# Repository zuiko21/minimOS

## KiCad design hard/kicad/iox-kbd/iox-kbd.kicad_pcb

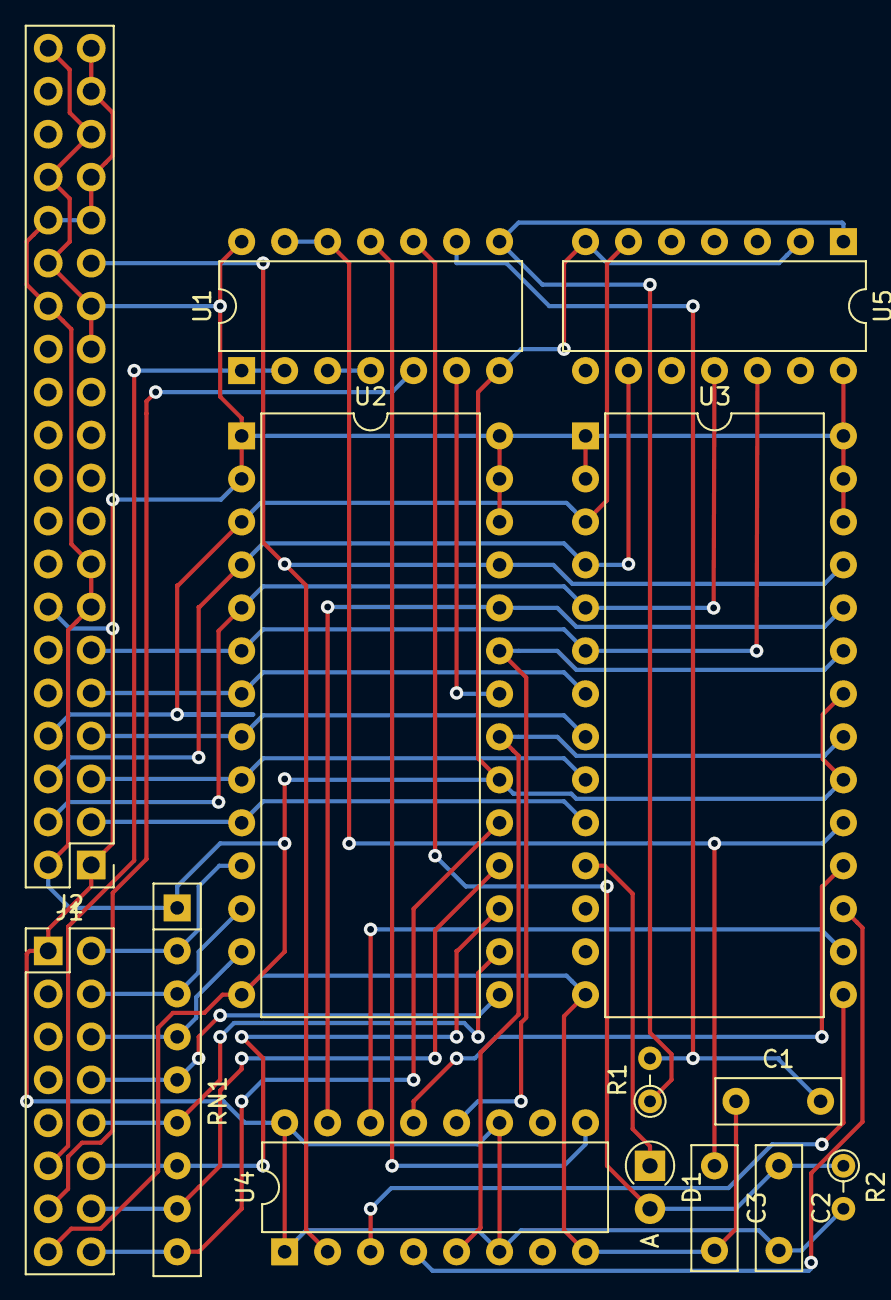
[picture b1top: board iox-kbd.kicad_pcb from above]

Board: 2 copper layers, 14 parts (0 on the bottom side), 36 nets.

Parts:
C1, C2, C3: C; C_Rect_L7.2mm_W2.5mm_P5.00mm_FKS2_FKP2_MKS2_MKP2
D1: 1N4148; D_A-405_P2.54mm_Vertical_AnodeUp
J1: IOX; PinHeader_2x08_P2.54mm_Vertical
J2: VIAport2; PinHeader_2x20_P2.54mm_Vertical
R1, R2: R; R_Axial_DIN0204_L3.6mm_D1.6mm_P2.54mm_Vertical
RN1: 220K; R_Array_SIP9
U1: 74HC132; DIP-14_W7.62mm
U2, U3: 27C512; DIP-28_W15.24mm
U4: 74HC174; DIP-16_W7.62mm
U5: 74HC4024; DIP-14_W7.62mm

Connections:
+5V: C2.2, J1.1, J2.1, J2.14, J2.25, J2.27, J2.30, J2.34, J2.35, J2.40, R2.2, U1.14, U2.1, U2.2, U2.26, U2.27, U2.28, U3.1, U3.2, U3.26, U3.27, U3.28, U4.1, U4.6, U4.11, U4.16, U5.14
/ALT: U3.18, U4.13
/CTL: U3.17, U4.4
/D0: J1.2, RN1.2, U2.11
/D1: J1.4, RN1.3, U2.12
/D2: J1.6, RN1.4, U2.13
/D3: J1.8, RN1.5, U2.15
/D4: J1.10, RN1.6, U2.16
/D5: J1.12, RN1.7, U2.17
/D6: J1.14, RN1.8, U2.18
/D7: J1.16, RN1.9, U2.19
/PA0: J2.3, U2.10, U3.10
/PA1: J2.5, U2.9, U3.9
/PA2: J2.7, U2.8, U3.8
/PA3: J2.9, U2.7, U3.7
/PA4: J2.11, U2.6, U3.6, U5.12
/PA5: J2.4, U2.5, U3.5, U5.11
/PA6: J2.6, U2.4, U3.4, U5.9
/PA7: J2.8, U2.3, U3.3, U5.6
/SHIFT: U3.16, U4.14
/~ACK: D1.1, U3.11
/~CAPS: U3.15, U4.3
/~CAPSLOCK: J2.29, U2.25, U3.25, U4.2
/~MOD: C3.1, U1.12, U1.13, U3.19
/~SEL: J1.11, U1.1, U1.2
/~WE: J1.13, U1.5
GND: C1.1, C3.2, J1.15, J2.2, J2.13, J2.15, J2.28, J2.31, J2.32, J2.33, J2.37, J2.39, RN1.1, U1.7, U2.14, U2.20, U3.14, U3.20, U3.22, U4.8, U5.2, U5.7
unnamed: C1.2, R1.2, U1.9
unnamed: C2.1, D1.2, R2.1, U1.10
unnamed: R1.1, U1.8, U5.1
unnamed: U1.3, U1.4
unnamed: U1.6, U2.22
unnamed: U1.11, U4.9
unnamed: U2.21, U3.21, U4.5
unnamed: U2.23, U3.23, U4.12
unnamed: U2.24, U3.24, U4.15

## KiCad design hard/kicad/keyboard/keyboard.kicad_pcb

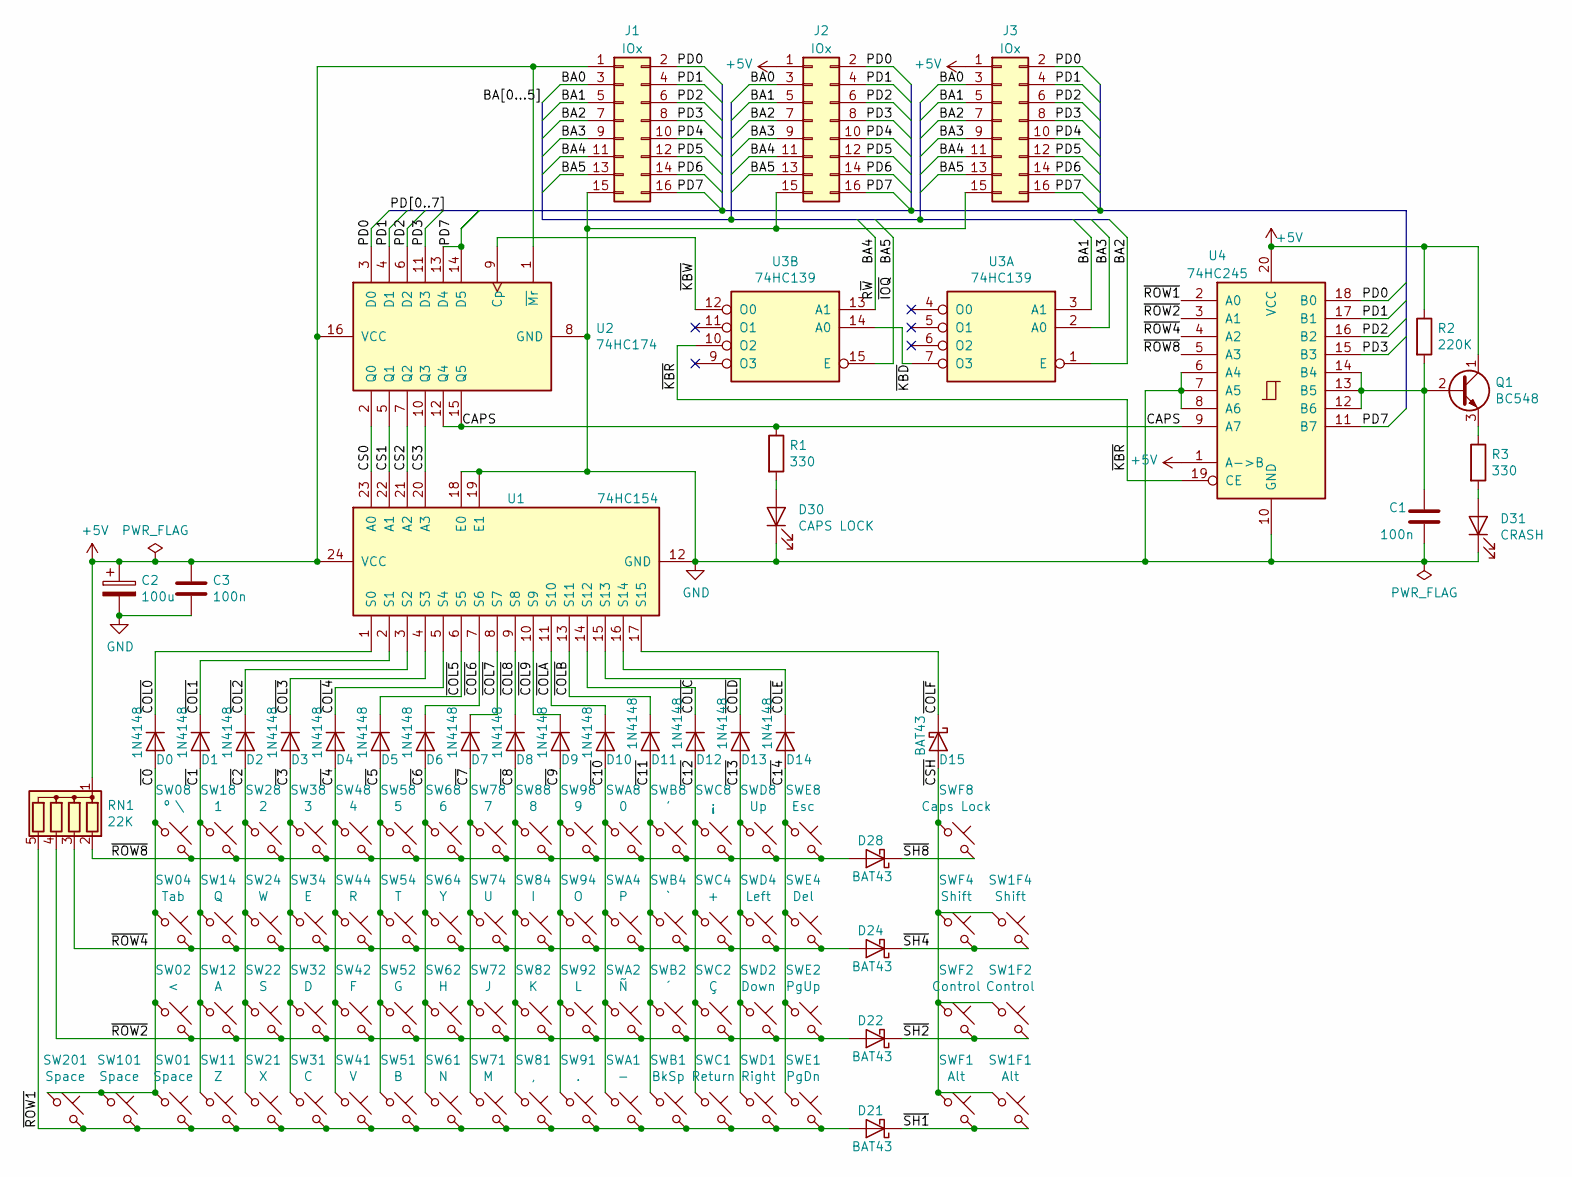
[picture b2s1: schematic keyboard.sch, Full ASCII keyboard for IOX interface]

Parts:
C1, C3: 100n; C_Rect_L7.2mm_W2.5mm_P5.00mm_FKS2_FKP2_MKS2_MKP2
C2: 100u; CP_Radial_D6.3mm_P2.50mm
D0, D1, D2, D3, D4, D5, D6, D7, D8, D9, D10, D11, D12, D13, D14: 1N4148; D_DO-35_SOD27_P7.62mm_Horizontal
D15, D21, D22, D24, D28: BAT43; D_DO-35_SOD27_P7.62mm_Horizontal
D30: CAPS LOCK; LED_D3.0mm
D31: CRASH; LED_D3.0mm
J1, J2, J3: IOx; IDC-Header_2x08_P2.54mm_Vertical
Q1: BC548; TO-92_Inline
R1, R3: 330; R_Axial_DIN0207_L6.3mm_D2.5mm_P10.16mm_Horizontal
R2: 220K; R_Axial_DIN0207_L6.3mm_D2.5mm_P10.16mm_Horizontal
RN1: 22K; R_Array_SIP5
SW01, SW101, SW201: Space; SW_PUSH-12mm
SW1F1: Alt; SW_PUSH-12mm
SW1F2: Control; SW_PUSH-12mm
SW1F4: Shift; SW_PUSH-12mm
SW02: <; SW_PUSH-12mm
SW04: Tab; SW_PUSH-12mm
SW08: º \\; SW_PUSH-12mm
SW11: Z; SW_PUSH-12mm
SW12: A; SW_PUSH-12mm
SW14: Q; SW_PUSH-12mm
SW18: 1; SW_PUSH-12mm
SW21: X; SW_PUSH-12mm
SW22: S; SW_PUSH-12mm
SW24: W; SW_PUSH-12mm
SW28: 2; SW_PUSH-12mm
SW31: C; SW_PUSH-12mm
SW32: D; SW_PUSH-12mm
SW34: E; SW_PUSH-12mm
SW38: 3; SW_PUSH-12mm
SW41: V; SW_PUSH-12mm
SW42: F; SW_PUSH-12mm
SW44: R; SW_PUSH-12mm
SW48: 4; SW_PUSH-12mm
SW51: B; SW_PUSH-12mm
SW52: G; SW_PUSH-12mm
SW54: T; SW_PUSH-12mm
SW58: 5; SW_PUSH-12mm
SW61: N; SW_PUSH-12mm
SW62: H; SW_PUSH-12mm
SW64: Y; SW_PUSH-12mm
SW68: 6; SW_PUSH-12mm
SW71: M; SW_PUSH-12mm
SW72: J; SW_PUSH-12mm
SW74: U; SW_PUSH-12mm
SW78: 7; SW_PUSH-12mm
SW81: ,; SW_PUSH-12mm
SW82: K; SW_PUSH-12mm
SW84: I; SW_PUSH-12mm
SW88: 8; SW_PUSH-12mm
SW91: .; SW_PUSH-12mm
SW92: L; SW_PUSH-12mm
SW94: O; SW_PUSH-12mm
SW98: 9; SW_PUSH-12mm
SWA1: -; SW_PUSH-12mm
SWA2: Ñ; SW_PUSH-12mm
SWA4: P; SW_PUSH-12mm
SWA8: 0; SW_PUSH-12mm
SWB1: BkSp; SW_PUSH-12mm
SWB2: ´; SW_PUSH-12mm
SWB4: `; SW_PUSH-12mm
SWB8: '; SW_PUSH-12mm
SWC1: Return; SW_PUSH-12mm
SWC2: Ç; SW_PUSH-12mm
SWC4: +; SW_PUSH-12mm
SWC8: ¡; SW_PUSH-12mm
SWD1: Right; SW_PUSH-12mm
SWD2: Down; SW_PUSH-12mm
SWD4: Left; SW_PUSH-12mm
SWD8: Up; SW_PUSH-12mm
SWE1: PgDn; SW_PUSH-12mm
SWE2: PgUp; SW_PUSH-12mm
SWE4: Del; SW_PUSH-12mm
SWE8: Esc; SW_PUSH-12mm
SWF1: Alt; SW_PUSH-12mm
SWF2: Control; SW_PUSH-12mm
SWF4: Shift; SW_PUSH-12mm
SWF8: Caps Lock; SW_PUSH-12mm
U1: 74HC154; DIP-24_W7.62mm_Socket
U2: 74HC174; DIP-16_W7.62mm_Socket
U3: 74HC139; DIP-16_W7.62mm_Socket
U4: 74HC245; DIP-20_W7.62mm

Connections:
+5V: C2.1, C3.1, J1.1, J2.1, J3.1, Q1.1 (C), R2.1, RN1.1 (common), U1.24 (VCC), U2.1 (~Mr), U2.16 (VCC), U4.1 (A->B), U4.20 (VCC)
/BA0: J1.3, J2.3, J3.3
/BA1: J1.5, J2.5, J3.5, U3.3 (A1)
/BA2: J1.7, J2.7, J3.7, U3.1 (E)
/BA3: J1.9, J2.9, J3.9, U3.2 (A0)
/BA4: J1.11, J2.11, J3.11, U3.13 (A1)
/BA5: J1.13, J2.13, J3.13, U3.15 (E)
/CAPS: R1.1, U2.12 (Q4), U2.15 (Q5), U4.9 (A7)
/CS0: U1.23 (A0), U2.2 (Q0)
/CS1: U1.22 (A1), U2.5 (Q1)
/CS2: U1.21 (A2), U2.7 (Q2)
/CS3: U1.20 (A3), U2.10 (Q3)
/PD0: J1.2, J2.2, J3.2, U2.3 (D0), U4.18 (B0)
/PD1: J1.4, J2.4, J3.4, U2.4 (D1), U4.17 (B1)
/PD2: J1.6, J2.6, J3.6, U2.6 (D2), U4.16 (B2)
/PD3: J1.8, J2.8, J3.8, U2.11 (D3), U4.15 (B3)
/PD4: J1.10, J2.10, J3.10
/PD5: J1.12, J2.12, J3.12
/PD6: J1.14, J2.14, J3.14
/PD7: J1.16, J2.16, J3.16, U2.13 (D4), U2.14 (D5), U4.11 (B7)
/~C0: D0.2 (A), SW01.1, SW02.1, SW04.1, SW08.1, SW101.1, SW201.1
/~C1: D1.2 (A), SW11.1, SW12.1, SW14.1, SW18.1
/~C2: D2.2 (A), SW21.1, SW22.1, SW24.1, SW28.1
/~C3: D3.2 (A), SW31.1, SW32.1, SW34.1, SW38.1
/~C4: D4.2 (A), SW41.1, SW42.1, SW44.1, SW48.1
/~C5: D5.2 (A), SW51.1, SW52.1, SW54.1, SW58.1
/~C6: D6.2 (A), SW61.1, SW62.1, SW64.1, SW68.1
/~C7: D7.2 (A), SW71.1, SW72.1, SW74.1, SW78.1
/~C8: D8.2 (A), SW81.1, SW82.1, SW84.1, SW88.1
/~C9: D9.2 (A), SW91.1, SW92.1, SW94.1, SW98.1
/~C10: D10.2 (A), SWA1.1, SWA2.1, SWA4.1, SWA8.1
/~C11: D11.2 (A), SWB1.1, SWB2.1, SWB4.1, SWB8.1
/~C12: D12.2 (A), SWC1.1, SWC2.1, SWC4.1, SWC8.1
/~C13: D13.2 (A), SWD1.1, SWD2.1, SWD4.1, SWD8.1
/~C14: D14.2 (A), SWE1.1, SWE2.1, SWE4.1, SWE8.1
/~COL0: D0.1 (K), U1.1 (S0)
/~COL1: D1.1 (K), U1.2 (S1)
/~COL2: D2.1 (K), U1.3 (S2)
/~COL3: D3.1 (K), U1.4 (S3)
/~COL4: D4.1 (K), U1.5 (S4)
/~COL5: D5.1 (K), U1.6 (S5)
/~COL6: D6.1 (K), U1.7 (S6)
/~COL7: D7.1 (K), U1.8 (S7)
/~COL8: D8.1 (K), U1.9 (S8)
/~COL9: D9.1 (K), U1.10 (S9)
/~COLA: D10.1 (K), U1.11 (S10)
/~COLB: D11.1 (K), U1.13 (S11)
/~COLC: D12.1 (K), U1.14 (S12)
/~COLD: D13.1 (K), U1.15 (S13)
/~COLE: D14.1 (K), U1.16 (S14)
/~COLF: D15.1 (K), U1.17 (S15)
/~CSH: D15.2 (A), SW1F1.1, SW1F2.1, SW1F4.1, SWF1.1, SWF2.1, SWF4.1, SWF8.1
/~KBD: U3.7 (O3), U3.14 (A0)
/~KBR: U3.10 (O2), U4.19 (CE)
/~KBW: U2.9 (Cp), U3.12 (O0)
/~ROW1: D21.2 (A), RN1.5 (R4), SW01.2, SW11.2, SW21.2, SW31.2, SW41.2, SW51.2, SW61.2, SW71.2, SW81.2, SW91.2, SW101.2, SW201.2, SWA1.2, SWB1.2, SWC1.2, SWD1.2, SWE1.2, U4.2 (A0)
/~ROW2: D22.2 (A), RN1.4 (R3), SW02.2, SW12.2, SW22.2, SW32.2, SW42.2, SW52.2, SW62.2, SW72.2, SW82.2, SW92.2, SWA2.2, SWB2.2, SWC2.2, SWD2.2, SWE2.2, U4.3 (A1)
/~ROW4: D24.2 (A), RN1.3 (R2), SW04.2, SW14.2, SW24.2, SW34.2, SW44.2, SW54.2, SW64.2, SW74.2, SW84.2, SW94.2, SWA4.2, SWB4.2, SWC4.2, SWD4.2, SWE4.2, U4.4 (A2)
/~ROW8: D28.2 (A), RN1.2 (R1), SW08.2, SW18.2, SW28.2, SW38.2, SW48.2, SW58.2, SW68.2, SW78.2, SW88.2, SW98.2, SWA8.2, SWB8.2, SWC8.2, SWD8.2, SWE8.2, U4.5 (A3)
/~SH1: D21.1 (K), SW1F1.2, SWF1.2
/~SH2: D22.1 (K), SW1F2.2, SWF2.2
/~SH4: D24.1 (K), SW1F4.2, SWF4.2
/~SH8: D28.1 (K), SWF8.2
GND: C1.2, C2.2, C3.2, D30.1 (K), D31.1 (K), J1.15, J2.15, J3.15, U1.12 (GND), U1.18 (E0), U1.19 (E1), U2.8 (GND), U4.6 (A4), U4.7 (A5), U4.8 (A6), U4.10 (GND)
unnamed: C1.1, Q1.2 (B), R2.2, U4.12 (B6), U4.13 (B5), U4.14 (B4)
unnamed: D30.2 (A), R1.2
unnamed: D31.2 (A), R3.2
unnamed: Q1.3 (E), R3.1

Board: 2 copper layers, 106 parts (0 on the bottom side), 68 nets, no tracks yet.

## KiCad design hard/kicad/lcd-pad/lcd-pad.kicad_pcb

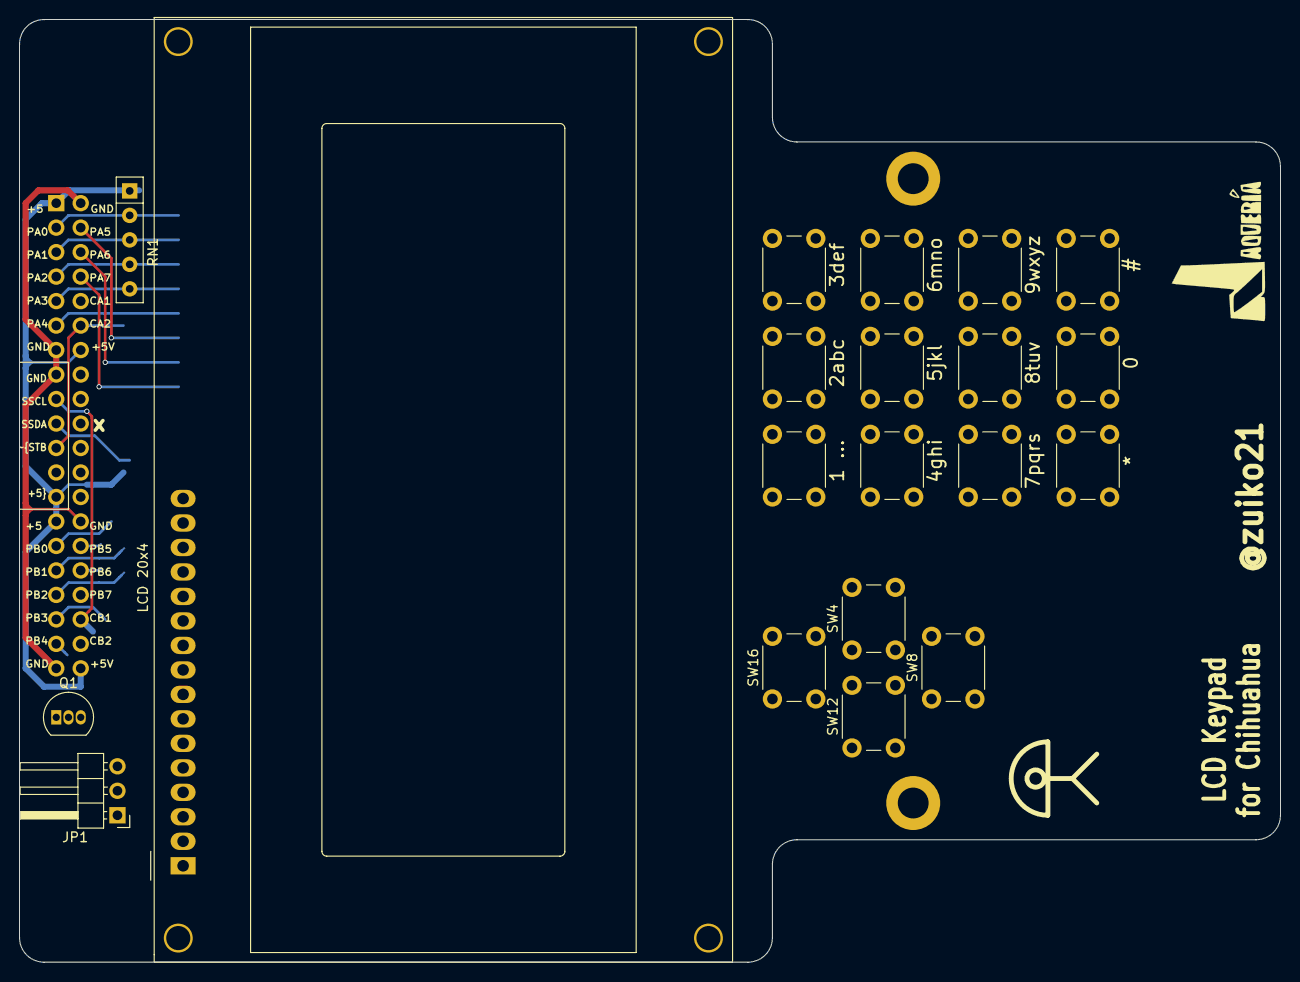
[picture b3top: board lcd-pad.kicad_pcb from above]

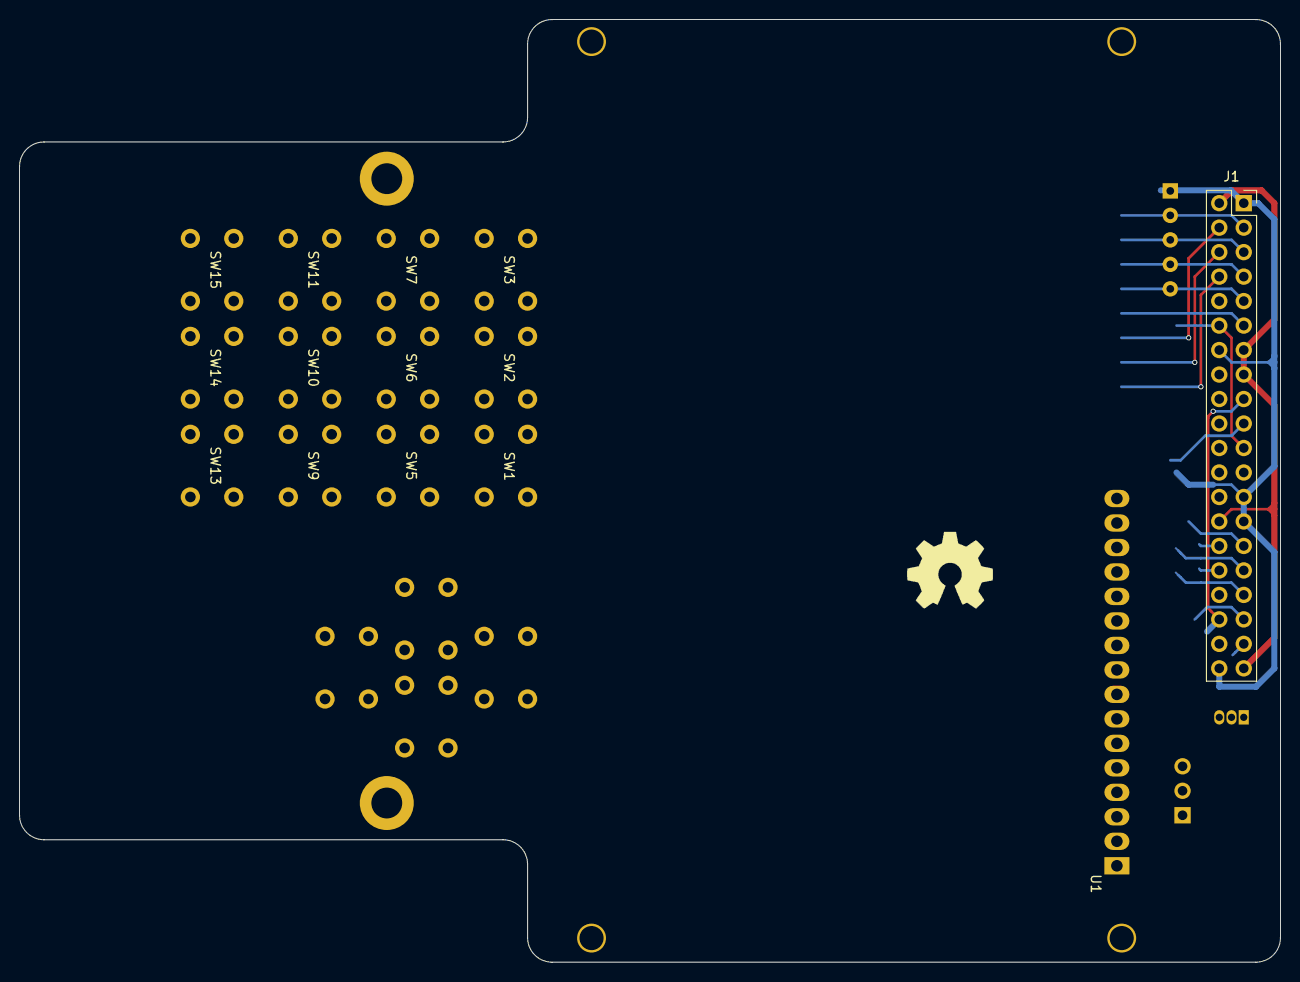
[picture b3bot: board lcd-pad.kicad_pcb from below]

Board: 2 copper layers, 130.8 x 97.8 mm, 25 parts (2 on the bottom side), 22 nets.

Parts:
H1, H2: MountingHole_Pad; MountingHole_3.2mm_M3_DIN965_Pad
J1: VIAport; PinSocket_2x20_P2.54mm_Vertical
JP1: AUTO/ON; PinHeader_1x03_P2.54mm_Horizontal
LOGO1: Logo_Open_Hardware_Large; OSHW-Symbol_8.9x8mm_SilkScreen
LOGO2: Logo_Open_Hardware_Small; jaqueria
Q1: BC558; TO-92_Inline
RN1: 4K7; R_Array_SIP5
SW1: 1 …; SW_PUSH_6mm
SW2: 2abc; SW_PUSH_6mm
SW3: 3def; SW_PUSH_6mm
SW4: Right; SW_PUSH_6mm
SW5: 4ghi; SW_PUSH_6mm
SW6: 5jkl; SW_PUSH_6mm
SW7: 6mno; SW_PUSH_6mm
SW8: Down; SW_PUSH_6mm
SW9: 7pqrs; SW_PUSH_6mm
SW10: 8tuv; SW_PUSH_6mm
SW11: 9wxyz; SW_PUSH_6mm
SW12: Left; SW_PUSH_6mm
SW13: *; SW_PUSH_6mm
SW14: 0; SW_PUSH_6mm
SW15: #; SW_PUSH_6mm
SW16: Up; SW_PUSH_6mm
U1: LCD 20x4; JHD204AO_LCD20x4

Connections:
+5V: J1.1, J1.14, J1.25, J1.27, J1.40, RN1.1, U1.2, U1.15
/BUF_LED: JP1.1, Q1.3
/CA2: J1.12, J1.21
/CB1: J1.17, J1.36
/CB2: J1.19, J1.38, Q1.2
/LED_K: JP1.2, U1.16
GND: H1.1, H2.1, J1.2, J1.13, J1.15, J1.28, J1.39, JP1.3, Q1.1, U1.1
PA0: J1.3, RN1.2, SW1.2, SW2.2, SW3.2, SW4.2
PA1: J1.5, RN1.3, SW5.2, SW6.2, SW7.2, SW8.2
PA2: J1.7, RN1.4, SW9.2, SW10.2, SW11.2, SW12.2
PA3: J1.9, RN1.5, SW13.2, SW14.2, SW15.2, SW16.2
PA4: J1.11, SW1.1, SW5.1, SW9.1, SW13.1
PA5: J1.4, SW2.1, SW6.1, SW10.1, SW14.1
PA6: J1.6, SW3.1, SW7.1, SW11.1, SW15.1
PA7: J1.8, SW4.1, SW8.1, SW12.1, SW16.1
PB0: J1.29, U1.6
PB1: J1.31, U1.4
PB2: J1.33, U1.5
PB4: J1.37, U1.11
PB5: J1.30, U1.12
PB6: J1.32, U1.13
PB7: J1.34, U1.14

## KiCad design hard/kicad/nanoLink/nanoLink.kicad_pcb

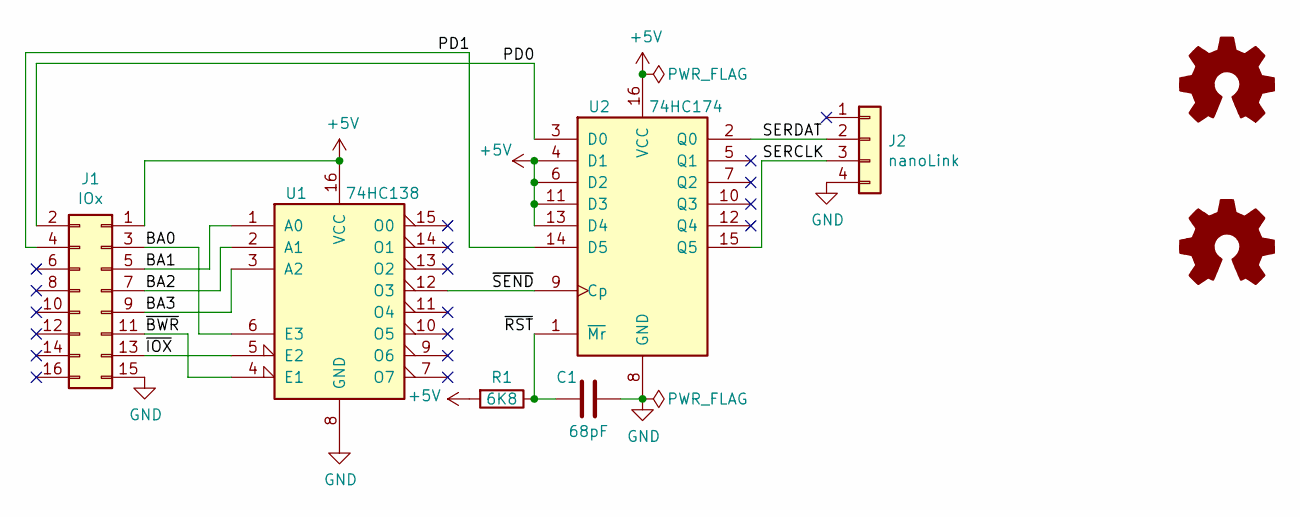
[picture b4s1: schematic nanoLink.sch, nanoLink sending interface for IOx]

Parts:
C1: 68pF; C_Disc_D3.8mm_W2.6mm_P2.50mm
J1: IOx; PinSocket_2x08_P2.54mm_Horizontal
J2: nanoLink; PinHeader_1x04_P2.54mm_Horizontal
LOGO1: Logo_Open_Hardware_Small; OSHW-Logo2_7.3x6mm_SilkScreen
LOGO2: Logo_Open_Hardware_Small; j300
R1: 6K8; R_Axial_DIN0207_L6.3mm_D2.5mm_P2.54mm_Vertical
U1: 74HC138; DIP-16_W7.62mm_Socket
U2: 74HC174; DIP-16_W7.62mm_Socket

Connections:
+5V: J1.1, R1.2, U1.16 (VCC), U2.4 (D1), U2.6 (D2), U2.11 (D3), U2.13 (D4), U2.16 (VCC)
/BA0: J1.3, U1.6 (E3)
/BA1: J1.5, U1.1 (A0)
/BA2: J1.7, U1.2 (A1)
/BA3: J1.9, U1.3 (A2)
/PD0: J1.2, U2.3 (D0)
/PD1: J1.4, U2.14 (D5)
/SERCLK: J2.3, U2.15 (Q5)
/SERDAT: J2.2, U2.2 (Q0)
/~BWR: J1.11, U1.4 (E1)
/~IOX: J1.13, U1.5 (E2)
/~RST: C1.2, R1.1, U2.1 (~Mr)
/~SEND: U1.12 (O3), U2.9 (Cp)
GND: C1.1, J1.15, J2.4, U1.8 (GND), U2.8 (GND)

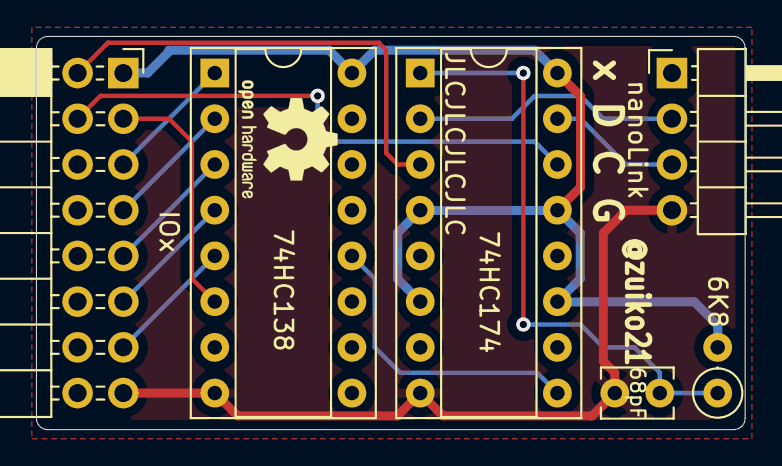
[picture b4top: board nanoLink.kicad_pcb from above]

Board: 2 copper layers, 39.4 x 21.8 mm, 8 parts (1 on the bottom side), 14 nets.

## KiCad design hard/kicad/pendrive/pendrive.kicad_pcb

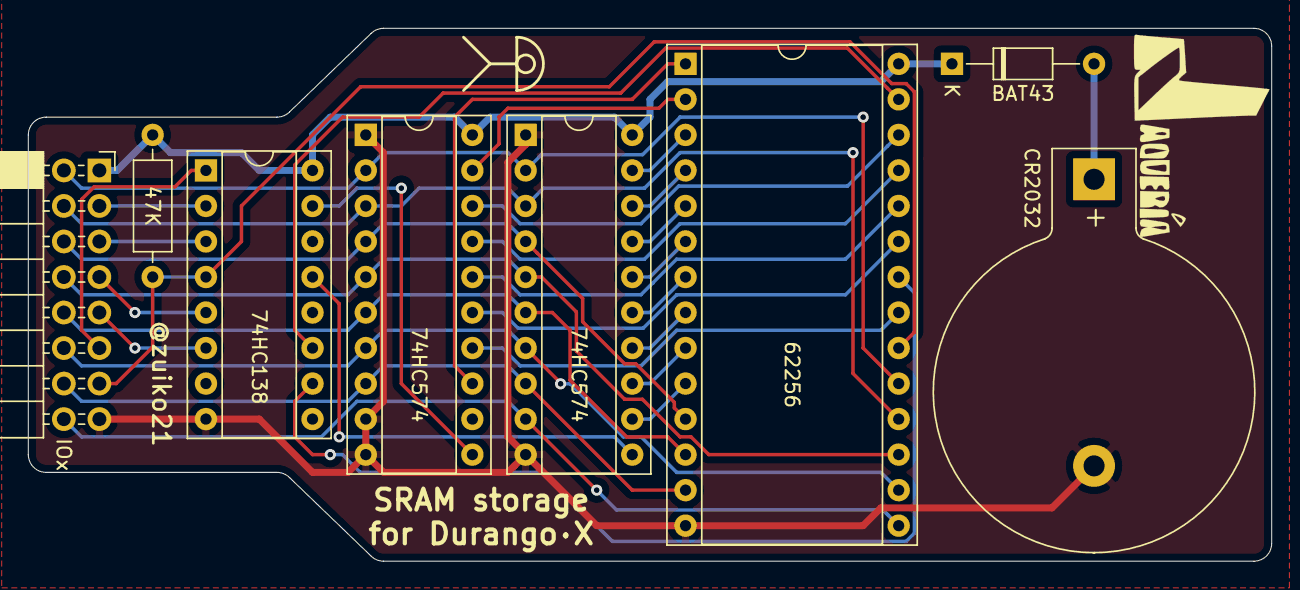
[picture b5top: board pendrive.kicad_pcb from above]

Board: 2 copper layers, 88.9 x 38.1 mm, 10 parts (1 on the bottom side), 36 nets.

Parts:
BT1: CR2032; BatteryHolder_Keystone_103_1x20mm
D1: BAT43; D_DO-35_SOD27_P10.16mm_Horizontal
J1: IOx; PinSocket_2x08_P2.54mm_Horizontal
LOGO1: Logo_Open_Hardware_Small; jaqueria
LOGO2: Logo_Open_Hardware_Large; OSHW-Logo_19x20mm_SilkScreen
R1: 47K; R_Axial_DIN0207_L6.3mm_D2.5mm_P10.16mm_Horizontal
U1: 62256; DIP-28_W15.24mm_Socket
U2: 74HC138; DIP-16_W7.62mm_Socket
U3, U4: 74HC574; DIP-20_W7.62mm_Socket

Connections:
+5V: D1.1, J1.1, R1.2, U1.28, U2.16, U3.20, U4.20
/A0: U1.3, U3.19
/A1: U1.4, U3.18
/A2: U1.5, U3.17
/A3: U1.6, U3.16
/A4: U1.7, U3.15
/A5: U1.8, U3.14
/A6: U1.9, U3.13
/A7: U1.10, U3.12
/A8: U1.2, U4.19
/A9: U1.26, U4.18
/A10: U1.25, U4.17
/A11: U1.24, U4.16
/A12: U1.23, U4.15
/A13: U1.21, U4.14
/A14: U1.1, U4.13
/BA0: J1.3, U2.2
/BA1: J1.5, U2.3
/BA2: J1.7, U2.5
/BA3: J1.9, U2.6
/PD0: J1.2, U1.19, U3.2, U4.2
/PD1: J1.4, U1.18, U3.3, U4.3
/PD2: J1.6, U1.11, U3.4, U4.4
/PD3: J1.8, U1.17, U3.5, U4.5
/PD4: J1.10, U1.12, U3.6, U4.6
/PD5: J1.12, U1.16, U3.7, U4.7
/PD6: J1.14, U1.13, U3.8, U4.8
/PD7: J1.16, U1.15, U3.9
/~BRW: J1.11, U2.1
/~IOX: J1.13, R1.1, U1.20, U2.4
/~LH: U2.15, U4.11
/~LL: U2.13, U3.11
/~OE: U1.22, U2.10
/~WE: U1.27, U2.11
GND: BT1.2, J1.15, U1.14, U2.8, U3.1, U3.10, U4.1, U4.9, U4.10
unnamed: BT1.1, D1.2

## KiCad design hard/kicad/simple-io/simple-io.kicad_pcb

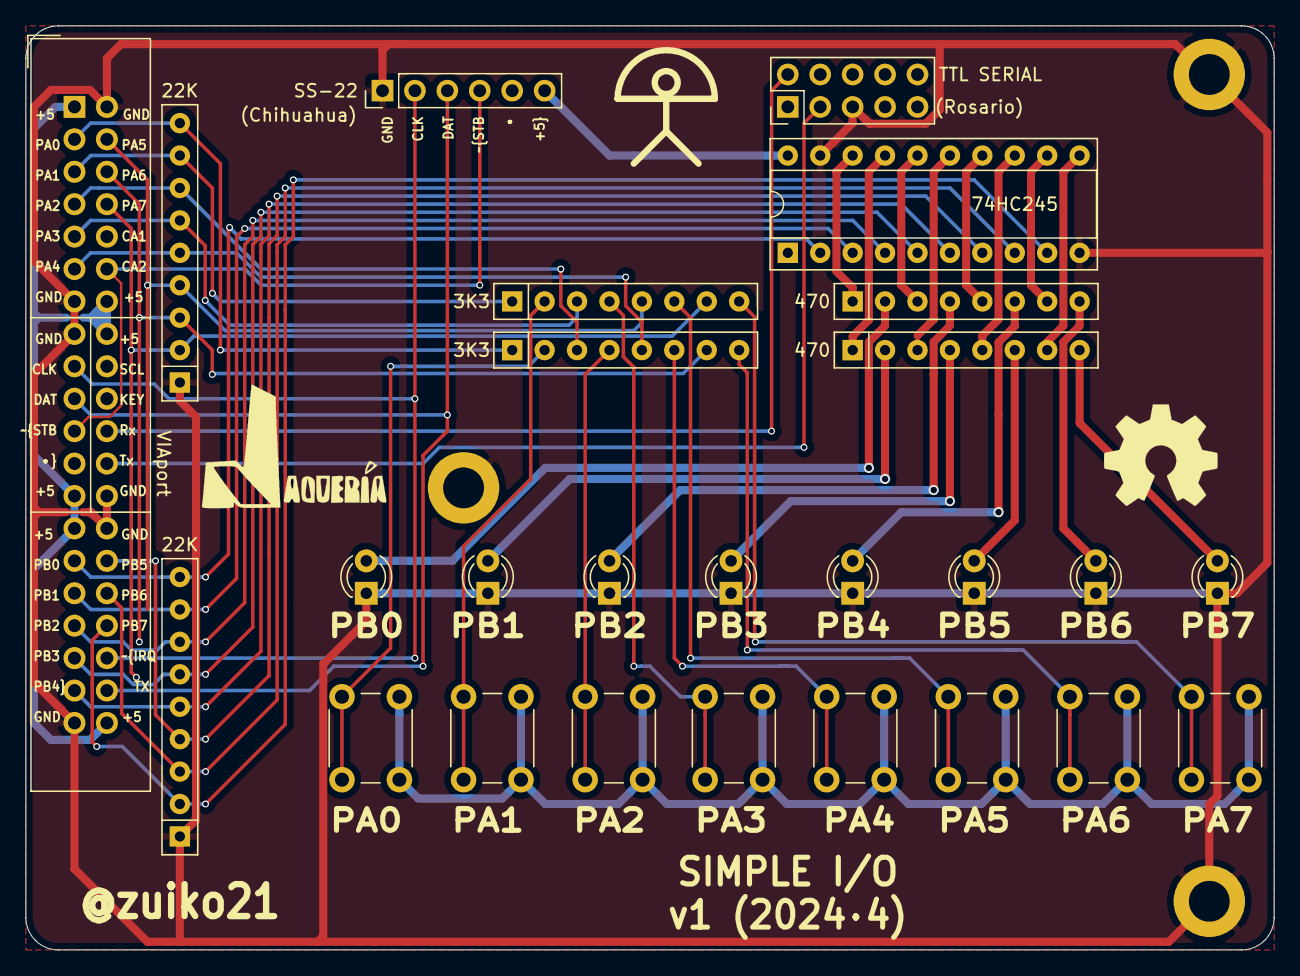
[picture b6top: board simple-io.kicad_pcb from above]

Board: 2 copper layers, 97.8 x 72.4 mm, 31 parts (0 on the bottom side), 47 nets.

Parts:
D1: PB0; LED_D3.0mm
D2: PB1; LED_D3.0mm
D3: PB2; LED_D3.0mm
D4: PB3; LED_D3.0mm
D5: PB4; LED_D3.0mm
D6: PB5; LED_D3.0mm
D7: PB6; LED_D3.0mm
D8: PB7; LED_D3.0mm
H1, H2, H3: MountingHole_Pad; MountingHole_3.2mm_M3_DIN965_Pad
J1: SS-22; PinHeader_1x06_P2.54mm_Vertical
J2: VIAport; IDC-Header_2x20_P2.54mm_Vertical
J3: TTL SERIAL; PinHeader_2x05_P2.54mm_Vertical
LOGO1: Logo_Open_Hardware_Large; OSHW-Symbol_8.9x8mm_SilkScreen
LOGO2: Logo_Open_Hardware_Small; jaqueria
RN1, RN6: 22K; R_Array_SIP9
RN2, RN3: 3K3; R_Array_SIP8
RN4, RN5: 470; R_Array_SIP8
SW1: PA0; SW_PUSH_6mm_H5mm
SW2: PA1; SW_PUSH_6mm_H5mm
SW3: PA2; SW_PUSH_6mm_H5mm
SW4: PA3; SW_PUSH_6mm_H5mm
SW5: PA4; SW_PUSH_6mm_H5mm
SW6: PA5; SW_PUSH_6mm_H5mm
SW7: PA6; SW_PUSH_6mm_H5mm
SW8: PA7; SW_PUSH_6mm_H5mm
U1: 74HC245; DIP-20_W7.62mm_Socket

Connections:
+5V: J1.6, J2.1, J2.14, J2.16, J2.25, J2.27, J2.40, SW1.2, SW2.2, SW3.2, SW4.2, SW5.2, SW6.2, SW7.2, SW8.2, U1.1, U1.20
/BB0: RN4.1, U1.18
/BB1: RN5.1, U1.17
/BB2: RN4.3, U1.16
/BB3: RN5.3, U1.15
/BB4: RN4.5, U1.14
/BB5: RN5.5, U1.13
/BB6: RN4.7, U1.12
/BB7: RN5.7, U1.11
/CA2: J1.4, J2.12, J2.21
/CB1: J1.2, J2.17, J2.36
/CB2: J1.3, J2.19, J2.38
/RA0: RN3.2, SW1.1
/RA1: RN2.2, SW2.1
/RA2: RN3.4, SW3.1
/RA3: RN2.4, SW4.1
/RA4: RN3.6, SW5.1
/RA5: RN2.6, SW6.1
/RA6: RN3.8, SW7.1
/RA7: RN2.8, SW8.1
/RB0: D1.2, RN4.2
/RB1: D2.2, RN5.2
/RB2: D3.2, RN4.4
/RB3: D4.2, RN5.4
/RB4: D5.2, RN4.6
/RB5: D6.2, RN5.6
/RB6: D7.2, RN4.8
/RB7: D8.2, RN5.8
/SC_RX: J2.22, J3.2
/SC_TX: J2.24, J3.3
GND: D1.1, D2.1, D3.1, D4.1, D5.1, D6.1, D7.1, D8.1, H1.1, H2.1, H3.1, J1.1, J2.2, J2.13, J2.15, J2.26, J2.28, J2.39, J3.5, RN1.1, RN6.1, U1.10, U1.19
PA0: J2.3, RN3.1, RN6.9
PA1: J2.5, RN2.1, RN6.8
PA2: J2.7, RN3.3, RN6.7
PA3: J2.9, RN2.3, RN6.6
PA4: J2.11, RN3.5, RN6.5
PA5: J2.4, RN2.5, RN6.4
PA6: J2.6, RN3.7, RN6.3
PA7: J2.8, RN2.7, RN6.2
PB0: J2.29, RN1.9, U1.2
PB1: J2.31, RN1.8, U1.3
PB2: J2.33, RN1.7, U1.4
PB3: J2.35, RN1.6, U1.5
PB4: J2.37, RN1.5, U1.6
PB5: J2.30, RN1.4, U1.7
PB6: J2.32, RN1.3, U1.8
PB7: J2.34, RN1.2, U1.9

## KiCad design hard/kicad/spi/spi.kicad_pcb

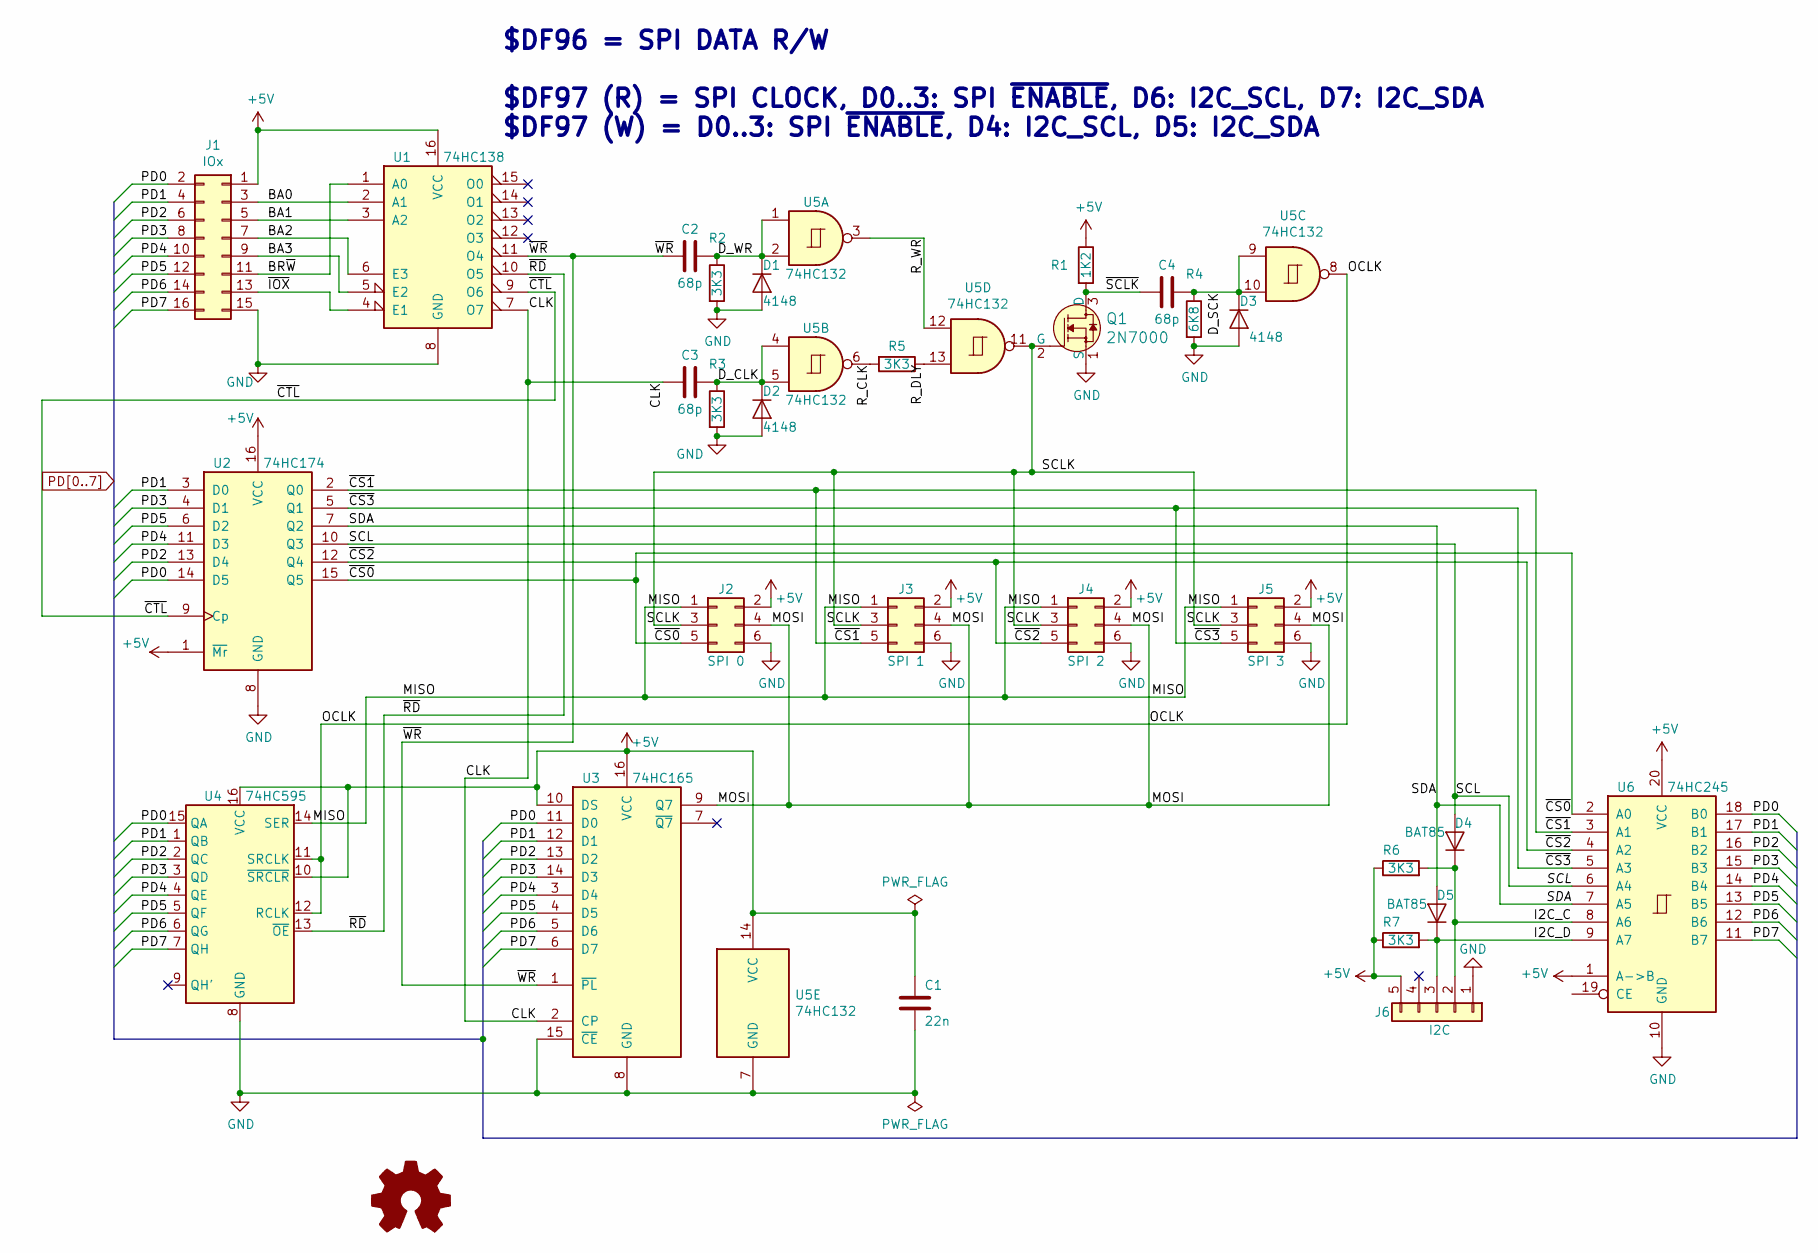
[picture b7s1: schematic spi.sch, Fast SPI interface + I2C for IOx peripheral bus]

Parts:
C1: 22n; C_Disc_D5.0mm_W2.5mm_P5.00mm
C2, C3, C4: 68p; C_Disc_D3.8mm_W2.6mm_P2.50mm
D1, D2, D3: 4148; D_DO-35_SOD27_P2.54mm_Vertical_AnodeUp
D4, D5: BAT85; D_DO-35_SOD27_P2.54mm_Vertical_KathodeUp
J1: IOx; PinSocket_2x08_P2.54mm_Horizontal
J2: SPI 0; IDC-Header_2x03_P2.54mm_Vertical
J3: SPI 1; IDC-Header_2x03_P2.54mm_Vertical
J4: SPI 2; IDC-Header_2x03_P2.54mm_Vertical
J5: SPI 3; IDC-Header_2x03_P2.54mm_Vertical
J6: I2C; PinHeader_1x05_P2.54mm_Horizontal
LOGO1: Logo_Open_Hardware_Small; j300
Q1: 2N7000; TO-92-3; MPN 2N7000; Digi-Key_PN 2N7000FS-ND
R1: 1K2; R_Axial_DIN0207_L6.3mm_D2.5mm_P2.54mm_Vertical
R2, R3, R5, R6, R7: 3K3; R_Axial_DIN0207_L6.3mm_D2.5mm_P2.54mm_Vertical
R4: 6K8; R_Axial_DIN0207_L6.3mm_D2.5mm_P2.54mm_Vertical
U1: 74HC138; DIP-16_W7.62mm_Socket
U2: 74HC174; DIP-16_W7.62mm_Socket
U3: 74HC165; DIP-16_W7.62mm_Socket
U4: 74HC595; DIP-16_W7.62mm_Socket
U5: 74HC132; DIP-14_W7.62mm_Socket
U6: 74HC245; DIP-20_W7.62mm_Socket

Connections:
+5V: C1.1, J1.1, J2.2, J3.2, J4.2, J5.2, J6.5, R1.1, R6.1, R7.1, U1.16 (VCC), U2.1 (~Mr), U2.16 (VCC), U3.10 (DS), U3.16 (VCC), U4.10 (~SRCLR), U4.16 (VCC), U5.14 (VCC), U6.1 (A->B), U6.20 (VCC)
/BA0: J1.3, U1.2 (A1)
/BA1: J1.5, U1.3 (A2)
/BA2: J1.7, U1.6 (E3)
/BA3: J1.9, U1.5 (E2)
/BR~W: J1.11, U1.1 (A0)
/CLK: C3.2, U1.7 (O7), U3.2 (CP)
/D_CLK: C3.1, D2.1 (K), R3.1, U5.4, U5.5
/D_SCK: C4.1, D3.1 (K), R4.1, U5.9, U5.10
/D_WR: C2.1, D1.1 (K), R2.1, U5.1, U5.2
/I2C_C: D4.1 (K), J6.2, R6.2, U6.8 (A6)
/I2C_D: D5.1 (K), J6.3, R7.2, U6.9 (A7)
/MISO: J2.1, J3.1, J4.1, J5.1, U4.14 (SER)
/MOSI: J2.4, J3.4, J4.4, J5.4, U3.9 (Q7)
/OCLK: U4.11 (SRCLK), U4.12 (RCLK), U5.8
/R_CLK: R5.2, U5.6
/R_DLY: R5.1, U5.13
/R_WR: U5.3, U5.12
/SCL: D4.2 (A), U2.10 (Q3), U6.6 (A4)
/SCLK: J2.3, J3.3, J4.3, J5.3, Q1.2 (G), U5.11
/SDA: D5.2 (A), U2.7 (Q2), U6.7 (A5)
/~CS0: J2.5, U2.15 (Q5), U6.2 (A0)
/~CS1: J3.5, U2.2 (Q0), U6.3 (A1)
/~CS2: J4.5, U2.12 (Q4), U6.4 (A2)
/~CS3: J5.5, U2.5 (Q1), U6.5 (A3)
/~CTL: U1.9 (O6), U2.9 (Cp)
/~IOX: J1.13, U1.4 (E1)
/~RD: U1.10 (O5), U4.13 (~OE)
/~SCLK: C4.2, Q1.3 (D), R1.2
/~WR: C2.2, U1.11 (O4), U3.1 (~PL)
GND: C1.2, D1.2 (A), D2.2 (A), D3.2 (A), J1.15, J2.6, J3.6, J4.6, J5.6, J6.1, Q1.1 (S), R2.2, R3.2, R4.2, U1.8 (GND), U2.8 (GND), U3.8 (GND), U3.15 (~CE), U4.8 (GND), U5.7 (GND), U6.10 (GND)
PD0: J1.2, U2.14 (D5), U3.11 (D0), U4.15 (QA), U6.18 (B0)
PD1: J1.4, U2.3 (D0), U3.12 (D1), U4.1 (QB), U6.17 (B1)
PD2: J1.6, U2.13 (D4), U3.13 (D2), U4.2 (QC), U6.16 (B2)
PD3: J1.8, U2.4 (D1), U3.14 (D3), U4.3 (QD), U6.15 (B3)
PD4: J1.10, U2.11 (D3), U3.3 (D4), U4.4 (QE), U6.14 (B4)
PD5: J1.12, U2.6 (D2), U3.4 (D5), U4.5 (QF), U6.13 (B5)
PD6: J1.14, U3.5 (D6), U4.6 (QG), U6.12 (B6)
PD7: J1.16, U3.6 (D7), U4.7 (QH), U6.11 (B7)

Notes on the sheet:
$DF96 = SPI DATA R/W $DF97 (R) = SPI CLOCK, D0..3: SPI ~ENABLE~, D6: I2C_SCL, D7: I2C_SDA $DF97 (W) = D0..3: SPI ~ENABLE~, D4: I2C_SCL, D5: I2C_SDA

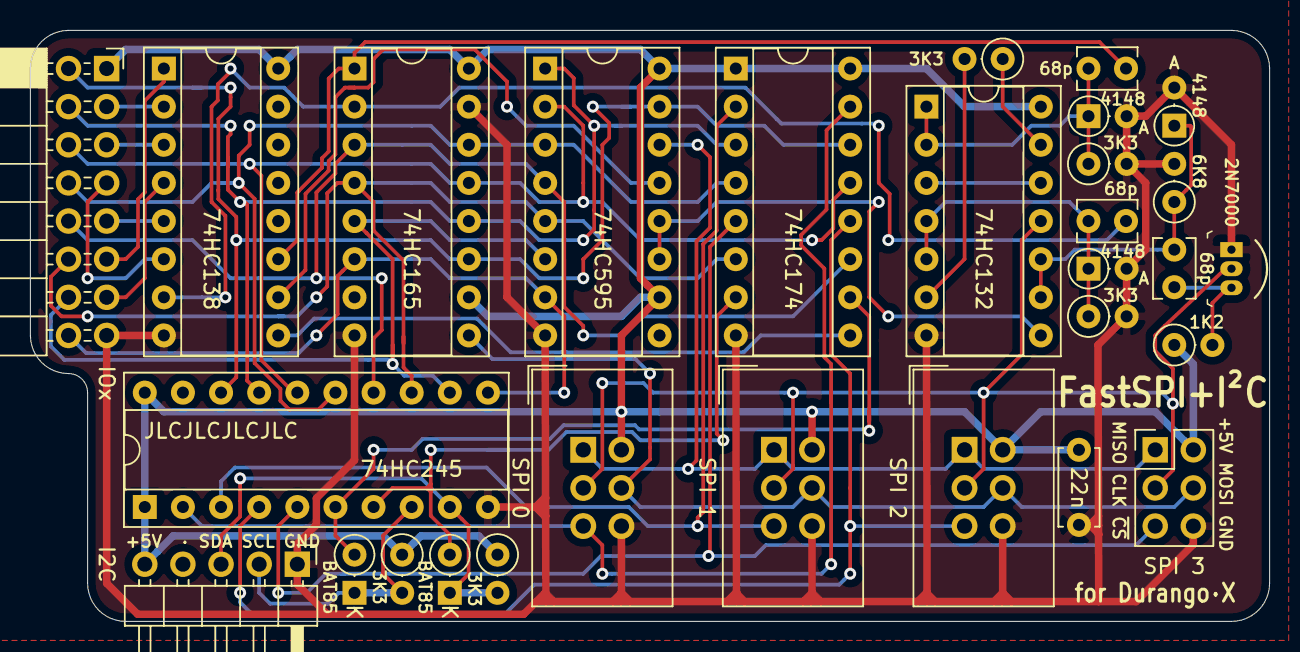
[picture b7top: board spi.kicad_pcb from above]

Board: 2 copper layers, 82.5 x 39.4 mm, 30 parts (1 on the bottom side), 39 nets.

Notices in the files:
hard/kicad/spi/spi.sch:
(c) 2023 Carlos J. Santisteban
